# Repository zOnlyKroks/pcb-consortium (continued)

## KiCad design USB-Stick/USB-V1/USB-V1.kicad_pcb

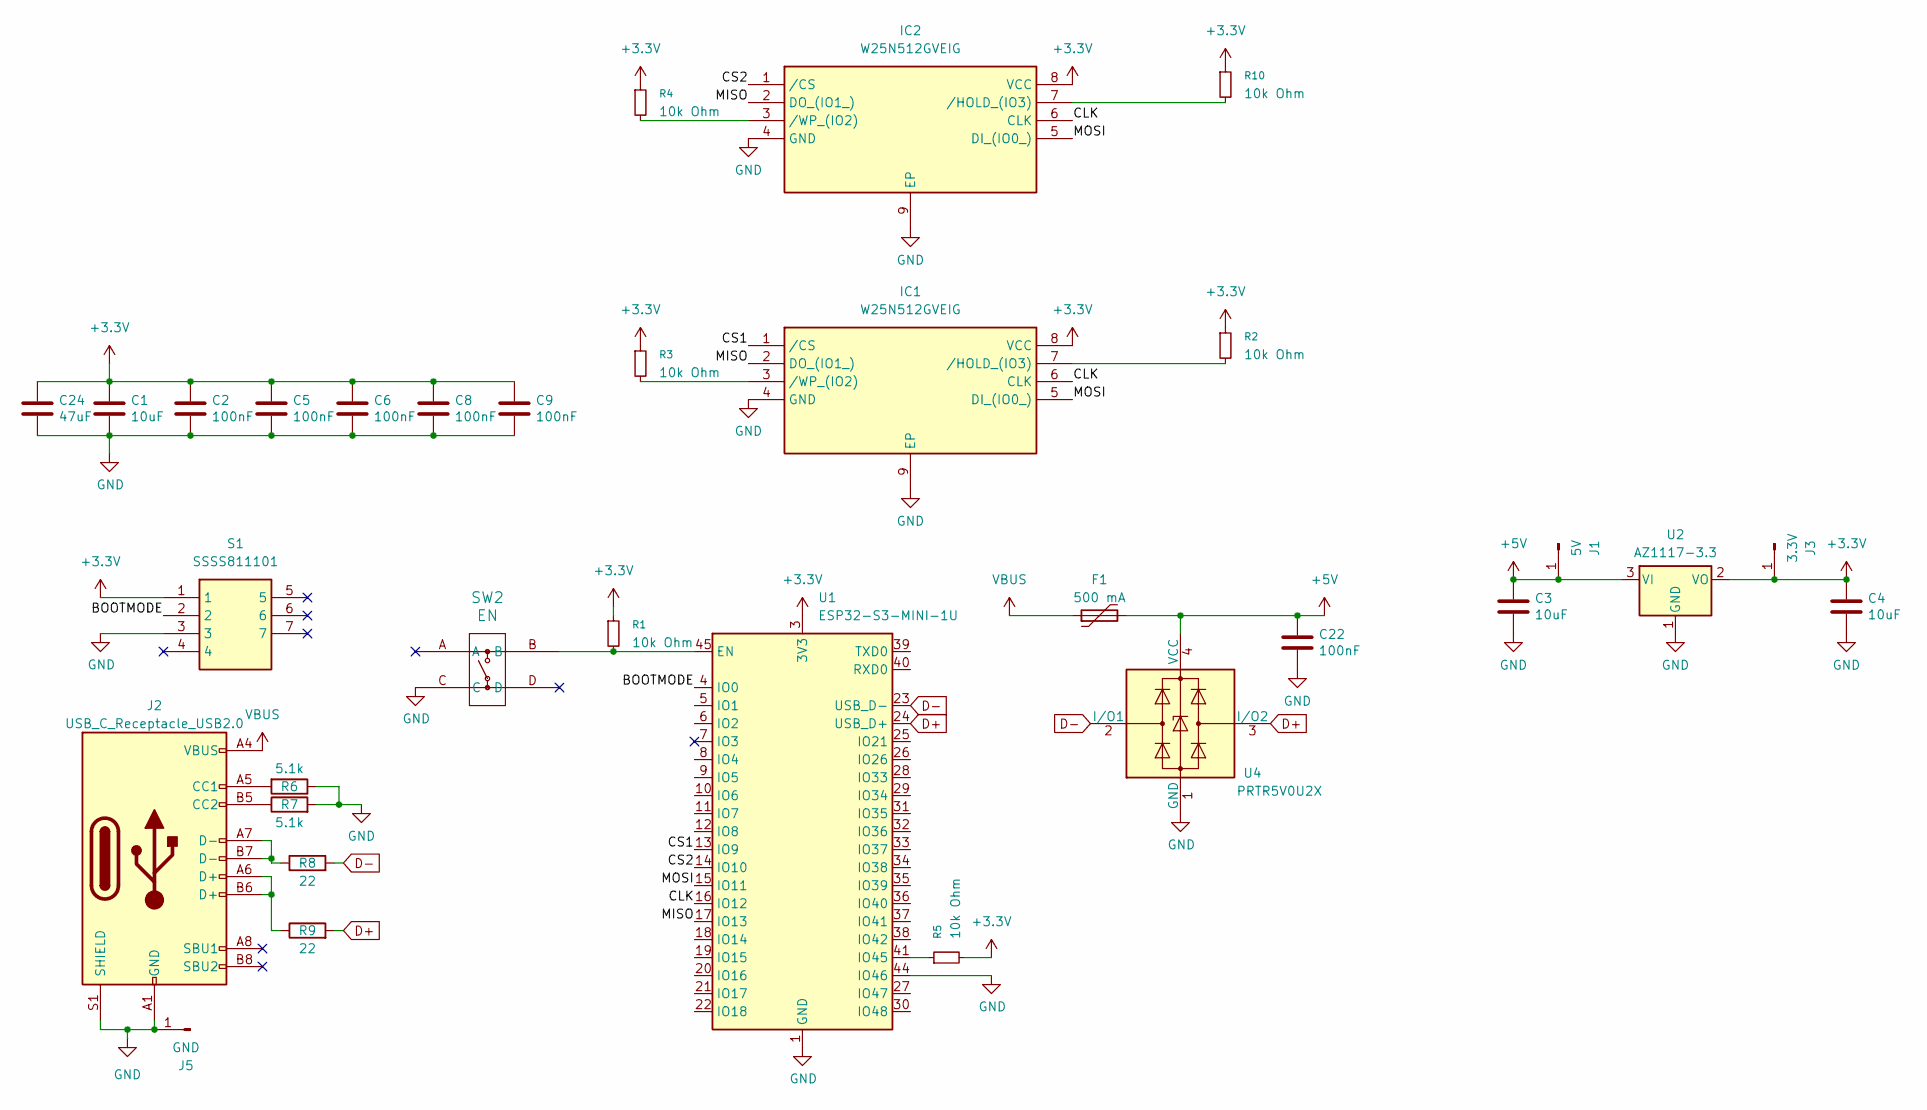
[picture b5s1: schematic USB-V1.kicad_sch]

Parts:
C1, C3, C4: 10uF; C_0603_1608Metric; LCSC C19702
C2, C5, C6, C8, C9, C22: 100nF; C_0603_1608Metric; LCSC C14663
C24: 47uF; C_1206_3216Metric; LCSC C96123
F1: 500 mA; Fuse_1206_3216Metric; LCSC C135341
IC1, IC2: W25N512GVEIG; Mouser Part Number 454-W25N512GVEIG
J1: 5V; PinHeader_1x01_P2.54mm_Vertical; LCSC Part # C492400
J2: USB_C_Receptacle_USB2.0; USB_C_Receptacle_HRO_TYPE-C-31-M-12; JlcRotOffset 180
J3: 3.3V; PinHeader_1x01_P2.54mm_Vertical; LCSC Part # C492400
J5: GND; PinHeader_1x01_P2.54mm_Vertical; LCSC Part # C492400
R1, R2, R3, R4, R5, R10: 10k Ohm; R_0603_1608Metric; LCSC Part # C98220
R6, R7: 5.1k; R_0603_1608Metric; LCSC Part # C23186
R8, R9: 22; R_0603_1608Metric; LCSC Part # C23345
S1: SSSS811101; Mouser Part Number 688-SSSS811101
SW2: EN; KH-6X6X5H-STM_SKE; LCSC Part # C2837531
U1: ESP32-S3-MINI-1U; ESP32-S2-MINI-1U
U2: AZ1117-3.3; TO-252-2; LCSC Part # C362112
U4: PRTR5V0U2X; SOT-143; LCSC C2827688

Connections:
+3.3V: C1.1, C2.1, C4.1, C5.1, C6.1, C8.1, C9.1, C24.1, IC1.8 (VCC), IC2.8 (VCC), J3.1, R1.1, R2.1, R3.1, R4.1, R5.2, R10.1, S1.1, U1.3 (3V3), U2.2 (VO)
+5V: C3.1, C22.1, F1.2, J1.1, U2.3 (VI), U4.4 (VCC)
/BOOTMODE: S1.2, U1.4 (IO0)
/CLK: IC1.6 (CLK), IC2.6 (CLK), U1.16 (IO12)
/CS1: IC1.1 (/CS), U1.13 (IO9)
/CS2: IC2.1 (/CS), U1.14 (IO10)
/MISO: IC1.2 (DO_(IO1_)), IC2.2 (DO_(IO1_)), U1.17 (IO13)
/MOSI: IC1.5 (DI_(IO0_)), IC2.5 (DI_(IO0_)), U1.15 (IO11)
D+: R9.2, U1.24 (USB_D+), U4.3 (I/O2)
D-: R8.2, U1.23 (USB_D-), U4.2 (I/O1)
GND: C1.2, C2.2, C3.2, C4.2, C5.2, C6.2, C8.2, C9.2, C22.2, C24.2, IC1.4 (GND), IC1.9 (EP), IC2.4 (GND), IC2.9 (EP), J2.A1 (GND), J2.A12 (GND), J2.B1 (GND), J2.B12 (GND), J2.S1 (SHIELD), J5.1, R6.1, R7.2, S1.3, SW2.C, U1.1 (GND), U1.2 (GND), U1.42 (GND), U1.43 (GND), U1.44 (IO46), U1.46 (GND), U1.47 (GND), U1.48 (GND), U1.49 (GND), U1.50 (GND), U1.51 (GND), U1.52 (GND), U1.53 (GND), U1.54 (GND), U1.55 (GND), U1.56 (GND), U1.57 (GND), U1.58 (GND), U1.59 (GND), U1.60 (GND), U1.61 (GND), U1.62 (GND), U1.63 (GND), U1.64 (GND), U1.65 (GND), U2.1 (GND), U4.1 (GND)
unnamed: IC1.7 (/HOLD_(IO3)), R2.2
unnamed: IC1.3 (/WP_(IO2)), R3.2
unnamed: IC2.7 (/HOLD_(IO3)), R10.2
unnamed: IC2.3 (/WP_(IO2)), R4.2
unnamed: J2.A5 (CC1), R6.2
unnamed: J2.B5 (CC2), R7.1
unnamed: J2.A6 (D+), J2.B6 (D+), R9.1
unnamed: J2.A7 (D-), J2.B7 (D-), R8.1
unnamed: R1.2, SW2.B, U1.45 (EN)
unnamed: R5.1, U1.41 (IO45)
VBUS: F1.1, J2.A4 (VBUS), J2.A9 (VBUS), J2.B4 (VBUS), J2.B9 (VBUS)

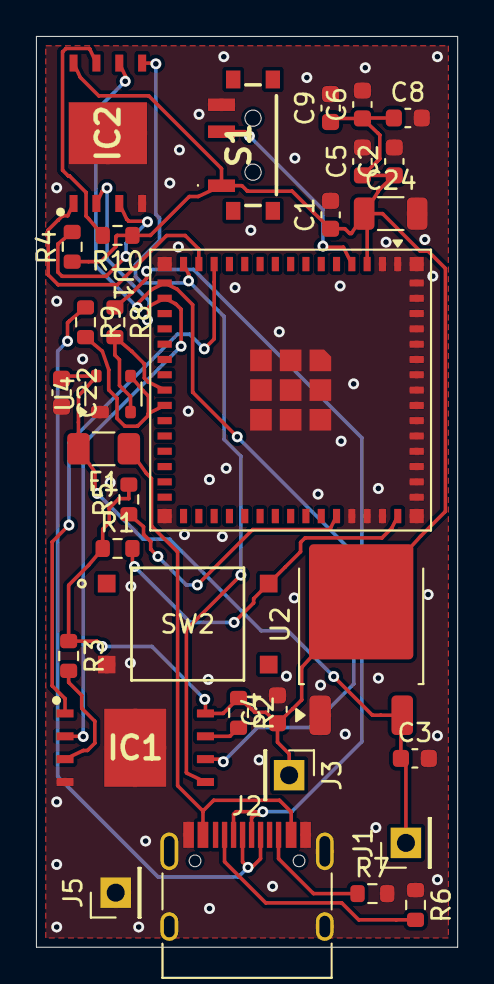
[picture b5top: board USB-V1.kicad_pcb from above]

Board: 2 copper layers, 23.4 x 50.6 mm, 32 parts (0 on the bottom side), 22 nets.

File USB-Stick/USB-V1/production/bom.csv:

Designator,Footprint,Quantity,Value,LCSC Part #
"C1, C3, C4",0603,3,10uF,C19702
"C2, C22, C5, C6, C8, C9",0603,6,100nF,C14663
C24,1206,1,47uF,C96123
F1,1206,1,500 mA,C135341
"IC1, IC2",W25N512GVEIG,2,W25N512GVEIG,C3024446
J1,PinHeader_1x01_P2.54mm_Vertical,1,5V,C492400
J2,USB_C_Receptacle_HRO_TYPE-C-31-M-12,1,USB_C_Receptacle_USB2.0,C165948
J3,PinHeader_1x01_P2.54mm_Vertical,1,3.3V,C492400
J5,PinHeader_1x01_P2.54mm_Vertical,1,GND,C492400
"R1, R10, R2, R3, R4, R5",0603,6,10k Ohm,C98220
"R6, R7",0603,2,5.1k,C23186
"R8, R9",0603,2,22,C23345
S1,SSSS811101,1,SSSS811101,C109335
SW2,KH-6X6X5H-STM_SKE,1,EN,C2837531 
U1,ESP32-S2-MINI-1U,1,ESP32-S3-MINI-1U,
U2,TO-252-2,1,AZ1117-3.3,
U4,SOT-143,1,PRTR5V0U2X,C2827688

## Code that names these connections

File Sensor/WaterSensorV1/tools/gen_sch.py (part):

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           fields=((71.12, 91.44, "left"), (71.12, 109.22, "left")))
    sh.wire((53.34, 99.06), "U1.1")
    sh.wire((48.26, 101.6), "U1.3")
    sh.label("USB_DN", (53.34, 88.9), 90)
    sh.label("USB_DP", (48.26, 88.9), 90)
    sh.power("VBUS", "U1.5")
    sh.power("GND", "U1.2")
    sh.label("USB_DN", sh.stub("U1.6", 7.62, 0))
    sh.label("USB_DP", sh.stub("U1.4", 7.62, 0))
    sh.nc("J1.A8")
    sh.nc("J1.B8")
    sh.wire("J1.A1", (30.48, 99.06))
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    sh.wire((332.74, 53.34), "Q3.3")
    sh.power("GND", "Q3.2")
    sh.wire("Q3.1", (312.42, 66.04))
    sh.label("VBAT_MEAS_EN", (312.42, 66.04), 180)
    R(sh, "R8", "1M", 317.5, 69.85, fields="L")
    sh.power("GND", "R8.2")
    R(sh, "R9", "100k", 345.44, 64.77)
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    sh.wire("R9.2", "R10.1")
    sh.power("GND", "R10.2")
    sh.wire((345.44, 71.12), (360.68, 71.12))
    sh.label("VBAT_ADC", (360.68, 71.12), 0)
    C(sh, "C6", "100nF", 353.06, 74.93)
    sh.power("GND", "C6.2")
    T("ADC = VBAT / 2 while VBAT_MEAS_EN is high", 302.26, 90.17)
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    sh.wire("R5.2", "R6.1")
    sh.power("GND", "R6.2")
    sh.wire((304.8, 97.79), (312.42, 97.79))
    sh.label("VBUS_DET", (312.42, 97.79), 0)

    # ------------------------------------------------ MCU
    T("ESP32-C6 (WiFi 6 / BLE / Zigbee / Thread)", 101.6, 154.94, 2, True)
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    sh.add("SW1", "WaterSensorV1:SW_Tact_4P", 104.14, 177.8, rot=90, value="RESET", fp=SWFP, lcsc="C318884",
           fields=((101.6, 176.53, "right"), (101.6, 179.07, "right")))
    sh.power("GND", "SW1.1")
    for pin, net in (("4", "VBAT_MEAS_EN"), ("5", "PROBE_EN_N"), ("6", "LED"), ("8", "VBAT_ADC"),
                     ("9", "PROBE_ADC"), ("13", "USB_DN"), ("14", "USB_DP")):
        sh.label(net, sh.stub("U4." + pin, -5.08, 0), 180)
    for pin in ("7", "11", "12", "16", "17", "18", "19", "20", "21", "22", "23"):
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    sh.power("GND", "SW2.1")
    sh.stub("U4.28", 2.54, 0)
    sh.power("GND", (167.64, 191.77), rot=90)
    for pin, net in (("27", "VBUS_DET"), ("26", "USER_BTN"), ("25", "TXD0"), ("24", "RXD0")):
        sh.label(net, sh.stub("U4." + pin, 5.08, 0), 0)
    T("IO8 high + IO9 low at reset = download mode", 101.6, 226.06)
    T("USB D-/D+ = IO12/IO13 (USB-Serial-JTAG)", 101.6, 229.87)
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    sh.wire("D2.1", (236.22, 177.8))
    sh.power("GND", (236.22, 177.8))
    sh.wire((205.74, 200.66), (226.06, 200.66))
    sh.label("USER_BTN", (205.74, 200.66), 180)
    R(sh, "R14", "100k", 218.44, 196.85, fields="L")
    sh.power("+3V3", "R14.1")
    sh.add("SW3", "WaterSensorV1:SW_Tact_4P", 226.06, 205.74, rot=90, value="USER", fp=SWFP, lcsc="C318884",
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    sh.wire("Q4.2", (325.12, 180.34))
    sh.power("+3V3", (325.12, 180.34))
    sh.wire("Q4.1", (335.28, 170.18), (307.34, 170.18))
    sh.label("PROBE_EN_N", (307.34, 170.18), 180)
    R(sh, "R16", "100k", 317.5, 166.37)
    sh.power("+3V3", "R16.1")
    sh.add("J3", "Connector_Generic:Conn_01x03", 360.68, 180.34, mirror="x", value="SOIL PROBE",
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    sh.wire("J3.3", (347.98, 177.8), (347.98, 154.94), (344.17, 154.94))
    R(sh, "R17", "1k", 340.36, 154.94, rot=90, fields="T")
    sh.wire("R17.1", (322.58, 154.94))
    sh.label("PROBE_ADC", (322.58, 154.94), 180)
    C(sh, "C9", "100nF", 330.2, 158.75)
    sh.power("GND", "C9.2")
    T("GND", 364.49, 183.515)
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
